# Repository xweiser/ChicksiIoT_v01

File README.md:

# ChicksiIoT_v01
Equip a Campingcar with a remote acecess

## Project motivation and purpose 
	1) Explore benefits to retrofit a camping car with IoT
	2) Use as basis to consider a business (selling devices-services)
	3) Prevent damage from camping car (see use case freezing and stealing)

## USE Cases and User Stories
The former project was: Wio GPS Tracker Seed 
### Former use cases
Use Cases of Wio GPS project
	1) Car is parked in the winter: Temperature drops below freezing point which will destroy water piping system: Reasons can be defect heater or heater disconnected from 230V supply
	2) Camping Car is parked and thiefs are entering the car to steal it or/and steal interior
	3) GPS coordination are tracked during a trip as an addition to the chicksi tagebuch (logbook)

### Use cases
	1) Refill fresh water tank 
	2) Replace butan gas tanks
	3) Pay the electrical bill - winter heating 
	4) Empty gray water tank
	5) Heat the camping car interior from remote
	6) Plan new trips based on the route of prior trips
	
### Unique Selling points
	1) Allows actions so that the water piping in winter is not destroyed  when a power out occurs
	2) Can be retrofit to old camping cars 
	3) Does not need to add cables
	4) Provides intrusion alert
	5) Alarms in case of gas leakage even if you are not in the car
	6) Informs you about the power consumption 
	7) Creates automatically a GPS logbock - so you can see where you have been
	8) Start remote the heating

## Customer Requirements
### The System shall
	1) Alarm the user when the inner temperature drops below a defined value (5 degree Celsius)
	2) The Temperature Limit must be adjustable anytime
	3) Measure the interior temperature & humidity
	4) Measure the outside temperature & humidity
	5) Detect motion in the campingcar interior 
	6) Alarm the user when butane gas is detected in the camping car interior
	7) Store the measured values
	8) Visualise the stored values
	9) Inform the user about the system Status on request (Battery voltage, measured values)
	10) Inform the user about the fill level of the butane gas tanks
	11) Inform the user about the fill level of the fresh tank while the tank gets filled
	12) Log the GPS coordinate when the vehicle is mooving - 
	13) Display the logged GPS coordinates on a map, according to selected dates
	14) Remotly controlled illuminate the car interior
	15) Remotly start the heating of the  car (enabled by alde heating)
	16) Write variables of interest (Temperature, Intrusion alert, Powerloss, etc (see above) into a log file (in case the cloud connection failed)
	17) Enter a night modus where the illumnation (buttons, display, lighning (neopixel) can be switched off

Nice to have or Future Requirement : Add a OBDII Adapter to the car and read motor values, speed, etc

## Non Functional Requirements
	1) The system shall indicate if connected to the cloud services
	2) The system shall enable debugging (Add display?)
	3) Test the power-loss function
	4) Test the alarming of the system
	5) Create an error and event Log- that can be analyzed later on
	6) The pcb board must have electrical contact pads to enable connecting measruement devices such as an oszilloscope for error detection (dont know the right wording)
	7) The board reset function needs to be accessible to the user (to reboot the board)
	8) In observation mode (no person in the campingcar) the display shall be deactived to save battery power (in case of main power loss) the system shall communicate to the cloud as long as possible 

## MVP - Minimal viable Product
In general a MVP describes a Solution which offers a minimal acceptable value for the user. In this case the Function: Alarm the user when the power is cut and the interior temperature falls below 5 degree, is defined as MVP. Thus the User can takes action and inform the Parkinglot owner to repair the power supply.
The satellite boxes can be added in a later stage.

### Requirements for the MVP
1) Measure the interior temperature & humidity
2) Measure the outside temperature
3) Alarm when power loss and temperature below 5*C using IFTT

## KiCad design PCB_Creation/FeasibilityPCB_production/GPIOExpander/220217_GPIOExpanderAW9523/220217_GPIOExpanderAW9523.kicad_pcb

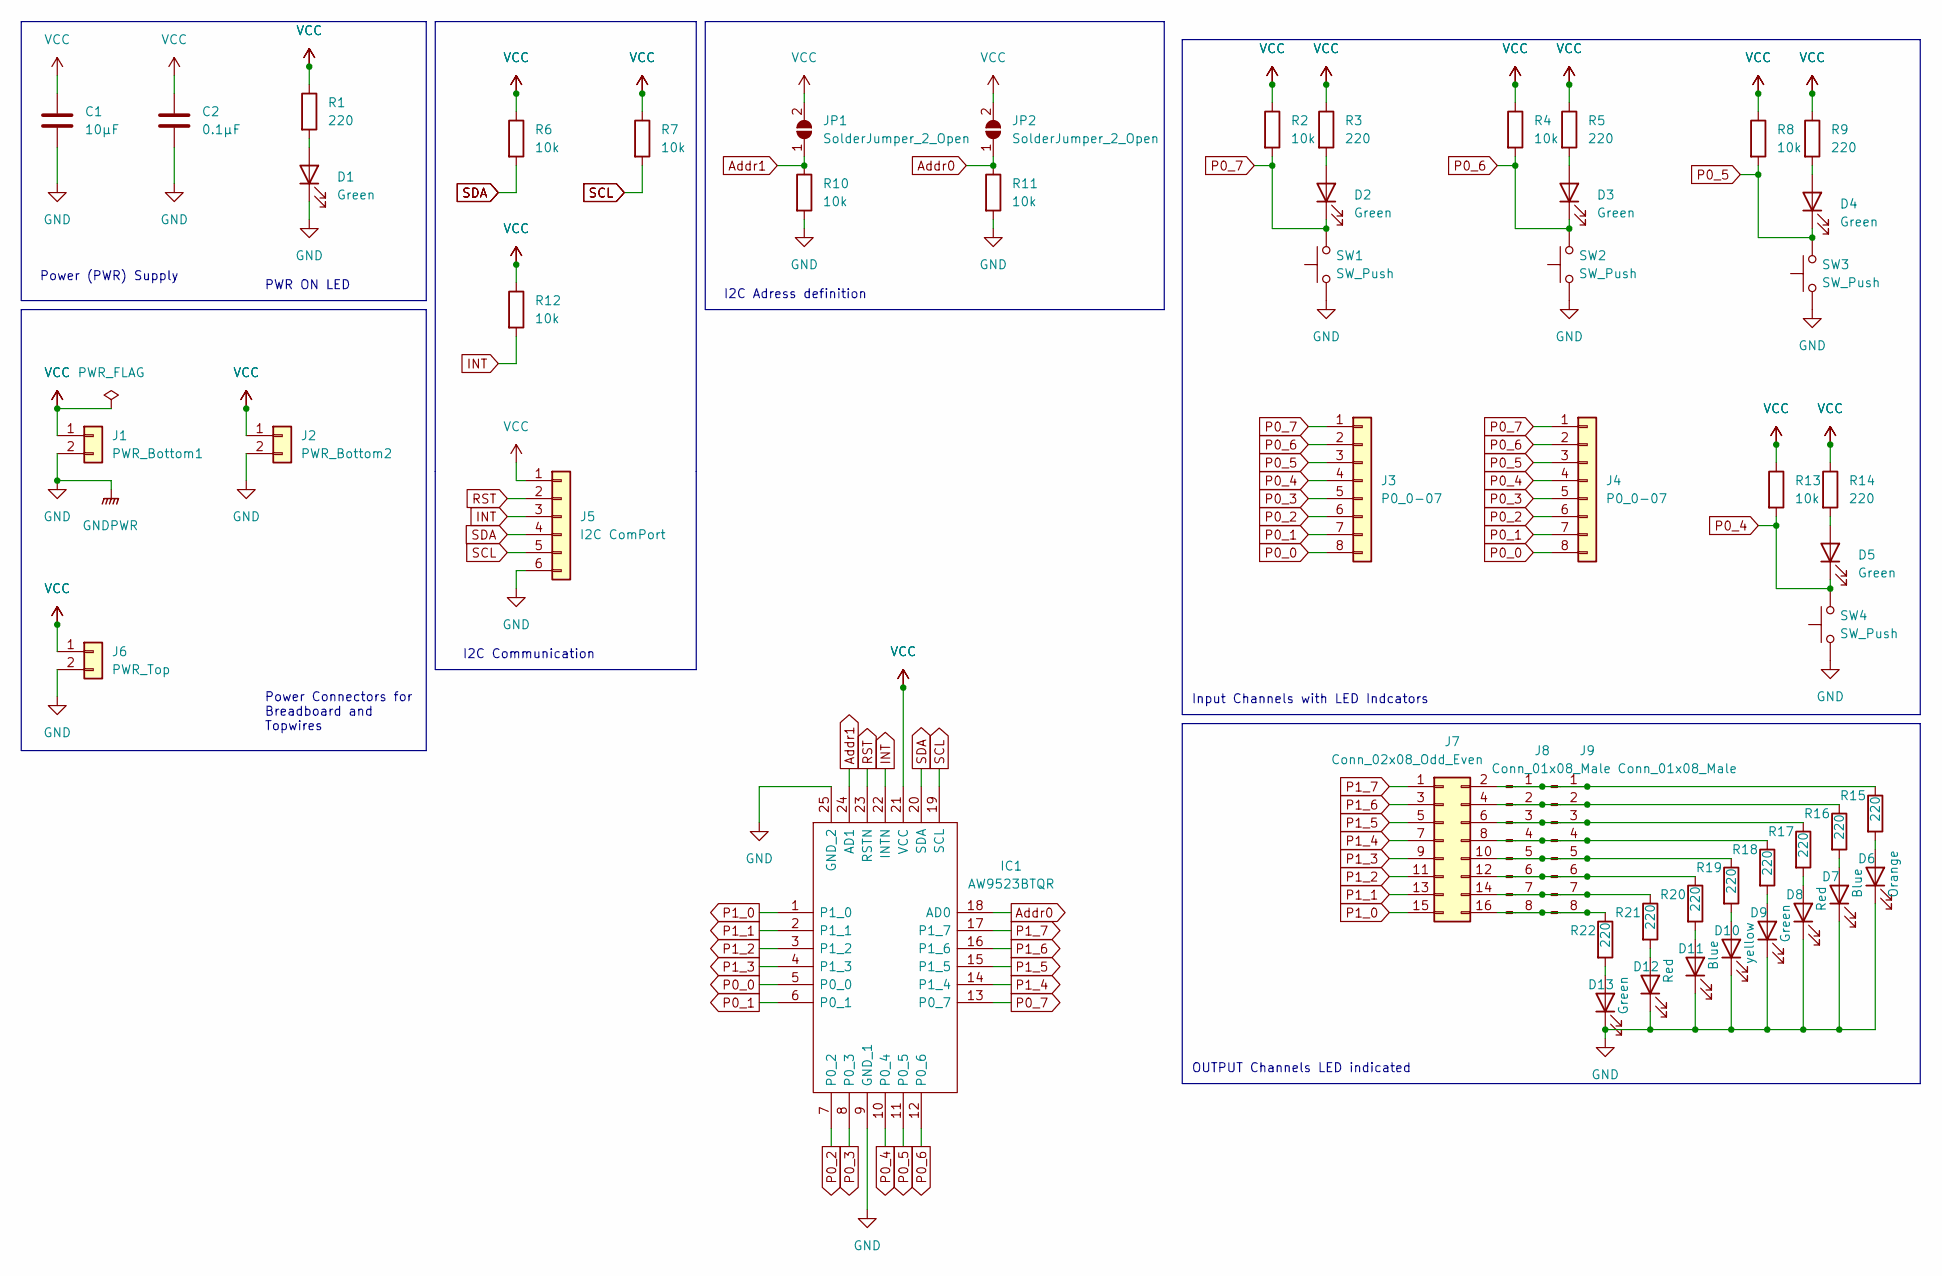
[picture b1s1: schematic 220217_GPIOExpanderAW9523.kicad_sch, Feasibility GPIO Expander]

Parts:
C1: 10µF; C_0805_2012Metric; Manufacturer_Part_Number LMK212ABJ106KG8T; LCSC LMK212ABJ106KG8T
C2: 0.1µF; C_0805_2012Metric; PartNumber C0805C104K5RAC7411; LCSC C0805C104K5RAC7411
D1, D2, D3, D4, D5, D9, D13: Green; LED_0805_2012Metric; Manufacturer_Part_Number APTD2012LZGCK; LCSC APTD2012LZGCK
D6: Orange; LED_0805_2012Metric; Manufacturer_Part_Number APT2012LSECK/J4-PRV; LCSC APT2012LSECK/J4-PRV
D7, D11: Blue; LED_0805_2012Metric; Manufacturer_Part_Number APTD2012LVBC/D; LCSC APTD2012LVBC/D
D8, D12: Red; LED_0805_2012Metric; Manufacturer_Part_Number APTD2012LSURCK; LCSC APTD2012LSURCK
D10: yellow; LED_0805_2012Metric; Manufacturer_Part_Number APTD2012LSYCK; LCSC APTD2012LSYCK
IC1: AW9523BTQR; QFN50P400X400X80-25N-D; Manufacturer_Part_Number AW9523BTQR; LCSC AW9523BTQR
J1: PWR_Bottom1; PinHeader_1x02_P2.54mm_Vertical
J2: PWR_Bottom2; PinHeader_1x02_P2.54mm_Vertical
J3: P0_0-07; PinHeader_1x08_P2.54mm_Vertical
J4: P0_0-07; PinHeader_1x08_P2.54mm_Vertical; Manufacturer_Part_Number M20-9990846; LCSC M20-9990846
J5: I2C ComPort; PinHeader_1x06_P2.54mm_Vertical
J6: PWR_Top; PinHeader_1x02_P2.54mm_Vertical
J7: Conn_02x08_Odd_Even; PinHeader_2x08_P2.54mm_Vertical; Manufacturer_Part_Number 5-146265-4; LCSC 5-146265-4
J8, J9: Conn_01x08_Male; PinHeader_1x08_P2.54mm_Vertical; Manufacturer_Part_Number M20-9990846; LCSC M20-9990846
JP1, JP2: SolderJumper_2_Open; SolderJumper-2_P1.3mm_Open_TrianglePad1.0x1.5mm
R1, R3, R5, R9, R14, R15, R16, R17, R18, R19, R20, R21, R22: 220; R_0805_2012Metric; Manufacturer_Part_Number ERJ-U06J221V; LCSC ERJ-U06J221V
R2, R4, R6, R7, R8, R10, R11, R12, R13: 10k; R_0805_2012Metric; Manufacturer_Part_Number ERJ-6GEYJ103V; LCSC ERJ-6GEYJ103V
SW1, SW2, SW3, SW4: SW_Push; 314375650; Manufacturer_Part_Number 3-1437565-0; LCSC 3-1437565-0

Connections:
Addr0: IC1.18 (AD0), JP2.1 (A), R11.1
Addr1: IC1.24 (AD1), JP1.1 (A), R10.1
GND: C1.2, C2.2, D1.1 (K), D6.1 (K), D7.1 (K), D8.1 (K), D9.1 (K), D10.1 (K), D11.1 (K), D12.1 (K), D13.1 (K), IC1.9 (GND_1), IC1.25 (GND_2), J1.2, J2.2, J5.6, J6.2, R10.2, R11.2, SW1.1, SW2.1, SW3.1, SW4.1
INT: IC1.22 (INTN), J5.3, R12.2
unnamed: D1.2 (A), R1.2
unnamed: D2.2 (A), R3.2
unnamed: D3.2 (A), R5.2
unnamed: D4.2 (A), R9.2
unnamed: D5.2 (A), R14.2
unnamed: D6.2 (A), R15.2
unnamed: D7.2 (A), R16.2
unnamed: D8.2 (A), R17.2
unnamed: D9.2 (A), R18.2
unnamed: D10.2 (A), R19.2
unnamed: D11.2 (A), R20.2
unnamed: D12.2 (A), R21.2
unnamed: D13.2 (A), R22.2
unnamed: J7.2, J8.1, J9.1, R15.1
unnamed: J7.4, J8.2, J9.2, R16.1
unnamed: J7.6, J8.3, J9.3, R17.1
unnamed: J7.8, J8.4, J9.4, R18.1
unnamed: J7.10, J8.5, J9.5, R19.1
unnamed: J7.12, J8.6, J9.6, R20.1
unnamed: J7.14, J8.7, J9.7, R21.1
unnamed: J7.16, J8.8, J9.8, R22.1
P0_0: IC1.5 (P0_0), J3.8, J4.8
P0_1: IC1.6 (P0_1), J3.7, J4.7
P0_2: IC1.7 (P0_2), J3.6, J4.6
P0_3: IC1.8 (P0_3), J3.5, J4.5
P0_4: D5.1 (K), IC1.10 (P0_4), J3.4, J4.4, R13.2, SW4.2
P0_5: D4.1 (K), IC1.11 (P0_5), J3.3, J4.3, R8.2, SW3.2
P0_6: D3.1 (K), IC1.12 (P0_6), J3.2, J4.2, R4.2, SW2.2
P0_7: D2.1 (K), IC1.13 (P0_7), J3.1, J4.1, R2.2, SW1.2
P1_0: IC1.1 (P1_0), J7.15
P1_1: IC1.2 (P1_1), J7.13
P1_2: IC1.3 (P1_2), J7.11
P1_3: IC1.4 (P1_3), J7.9
P1_4: IC1.14 (P1_4), J7.7
P1_5: IC1.15 (P1_5), J7.5
P1_6: IC1.16 (P1_6), J7.3
P1_7: IC1.17 (P1_7), J7.1
RST: IC1.23 (RSTN), J5.2
SCL: IC1.19 (SCL), J5.5, R7.2
SDA: IC1.20 (SDA), J5.4, R6.2
VCC: C1.1, C2.1, IC1.21 (VCC), J1.1, J2.1, J5.1, J6.1, JP1.2 (B), JP2.2 (B), R1.1, R2.1, R3.1, R4.1, R5.1, R6.1, R7.1, R8.1, R9.1, R12.1, R13.1, R14.1

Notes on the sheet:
I2C Communication
PWR ON LED
Input Channels with LED Indcators
Power (PWR) Supply
I2C Adress definition
Power Connectors for Breadboard and Topwires
OUTPUT Channels LED indicated

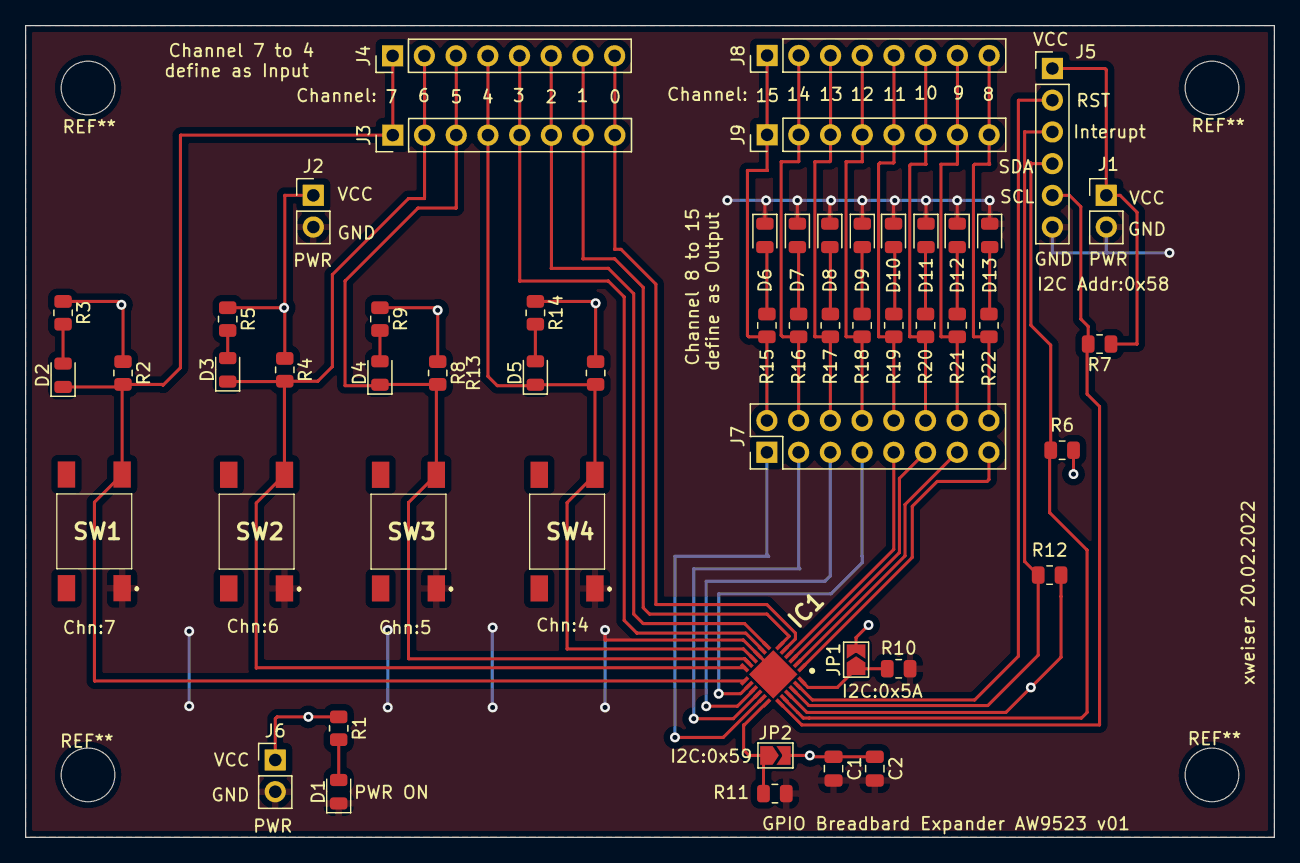
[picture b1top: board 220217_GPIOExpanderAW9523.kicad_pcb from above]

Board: 2 copper layers, 100.0 x 65.0 mm, 53 parts (0 on the bottom side), 45 nets.

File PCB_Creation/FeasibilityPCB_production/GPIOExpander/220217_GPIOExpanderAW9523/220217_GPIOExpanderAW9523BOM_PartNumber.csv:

Comment,Designator,Footprint,LCSC
"10µF","C1","Capacitor_SMD:C_0805_2012Metric","LMK212ABJ106KG8T"
"0.1µF","C2","Capacitor_SMD:C_0805_2012Metric","C0805C104K5RAC7411"
"Green","D1,D2,D3,D4,D5,D9,D13","LED_SMD:LED_0805_2012Metric","APTD2012LZGCK"
"yellow","D10","LED_SMD:LED_0805_2012Metric","APTD2012LSYCK"
"Orange","D6","LED_SMD:LED_0805_2012Metric","APT2012LSECK/J4-PRV"
"Blue","D7,D11","LED_SMD:LED_0805_2012Metric","APTD2012LVBC/D"
"Red","D8,D12","LED_SMD:LED_0805_2012Metric","APTD2012LSURCK"
"AW9523BTQR","IC1","SamacSys_Parts:QFN50P400X400X80-25N-D","AW9523BTQR"
"PWR_Bottom1","J1","Connector_PinHeader_2.54mm:PinHeader_1x02_P2.54mm_Vertical",""
"PWR_Bottom2","J2","Connector_PinHeader_2.54mm:PinHeader_1x02_P2.54mm_Vertical",""
"P0_0-07","J3,J4","Connector_PinHeader_2.54mm:PinHeader_1x08_P2.54mm_Vertical",""
"I2C ComPort","J5","Connector_PinHeader_2.54mm:PinHeader_1x06_P2.54mm_Vertical",""
"PWR_Top","J6","Connector_PinHeader_2.54mm:PinHeader_1x02_P2.54mm_Vertical",""
"Conn_02x08_Odd_Even","J7","Connector_PinHeader_2.54mm:PinHeader_2x08_P2.54mm_Vertical","5-146265-4 "
"Conn_01x08_Male","J8,J9","Connector_PinHeader_2.54mm:PinHeader_1x08_P2.54mm_Vertical","M20-9990846 "
"SolderJumper_2_Open","JP1,JP2","Jumper:SolderJumper-2_P1.3mm_Open_TrianglePad1.0x1.5mm",""
"220","R1,R3,R5,R9,R14,R15,R16,R17,R18,R19,R20,R21,R22","Resistor_SMD:R_0805_2012Metric","ERJ-U06J221V"
"10k","R2,R4,R6,R7,R8,R10,R11,R12,R13","Resistor_SMD:R_0805_2012Metric","ERJ-6GEYJ103V "
"SW_Push","SW1,SW2,SW3,SW4","SamacSys_Parts:314375650","3-1437565-0 "

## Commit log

2022-02-17 Update README.md
    First release - incomplete
2022-02-20 Version v01 completed
    Ordered at JLCPB
2022-02-20 last update from local
2022-03-03 MCU Folder Added
2022-03-03 Just a test
2022-03-03 Added PlattformIO Project - Empty
2022-03-04 testing the github sync with plattformiio
2022-04-09 Datasheet for the Controller to enable bugfixing
2022-04-09 First Test failed - board is not working
2022-04-09 Board is not working
2022-04-09 bkup deleted
    , because cannot be cloned - filename to long
2022-04-09 Added Non Functional Requirement for the PCB
2022-04-09 Started with version 2 - not finished yet
2022-04-10 Non Functional requirements added
